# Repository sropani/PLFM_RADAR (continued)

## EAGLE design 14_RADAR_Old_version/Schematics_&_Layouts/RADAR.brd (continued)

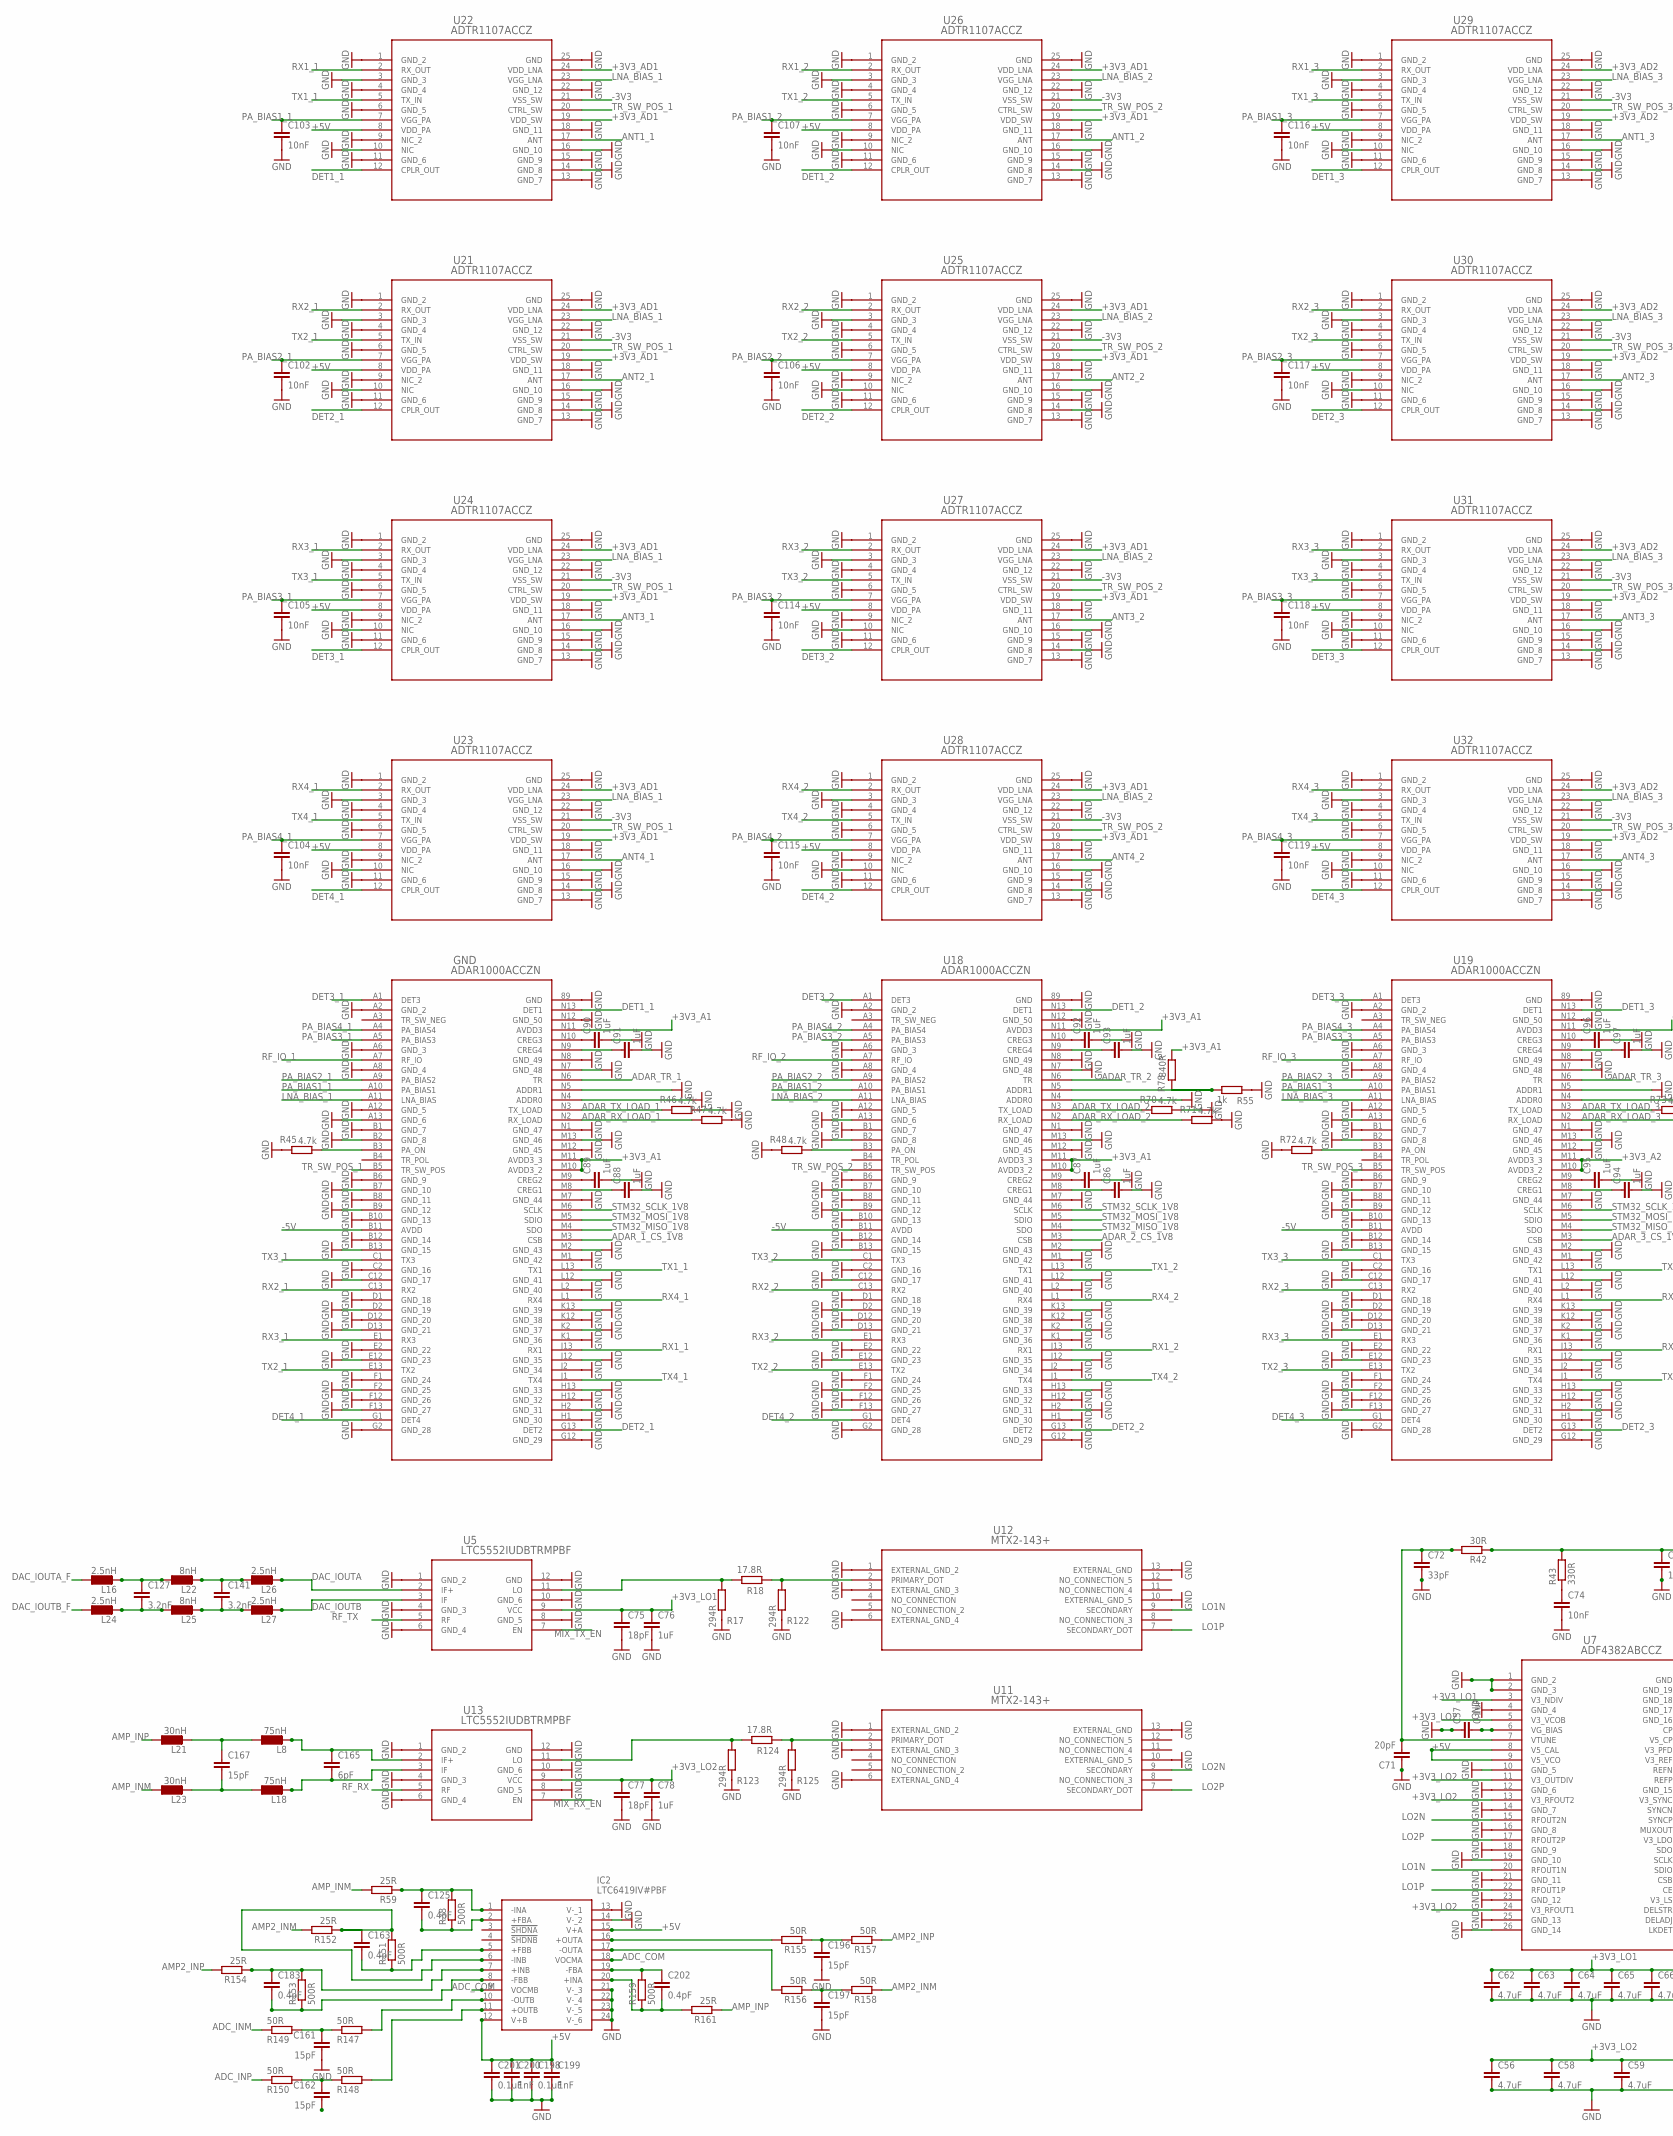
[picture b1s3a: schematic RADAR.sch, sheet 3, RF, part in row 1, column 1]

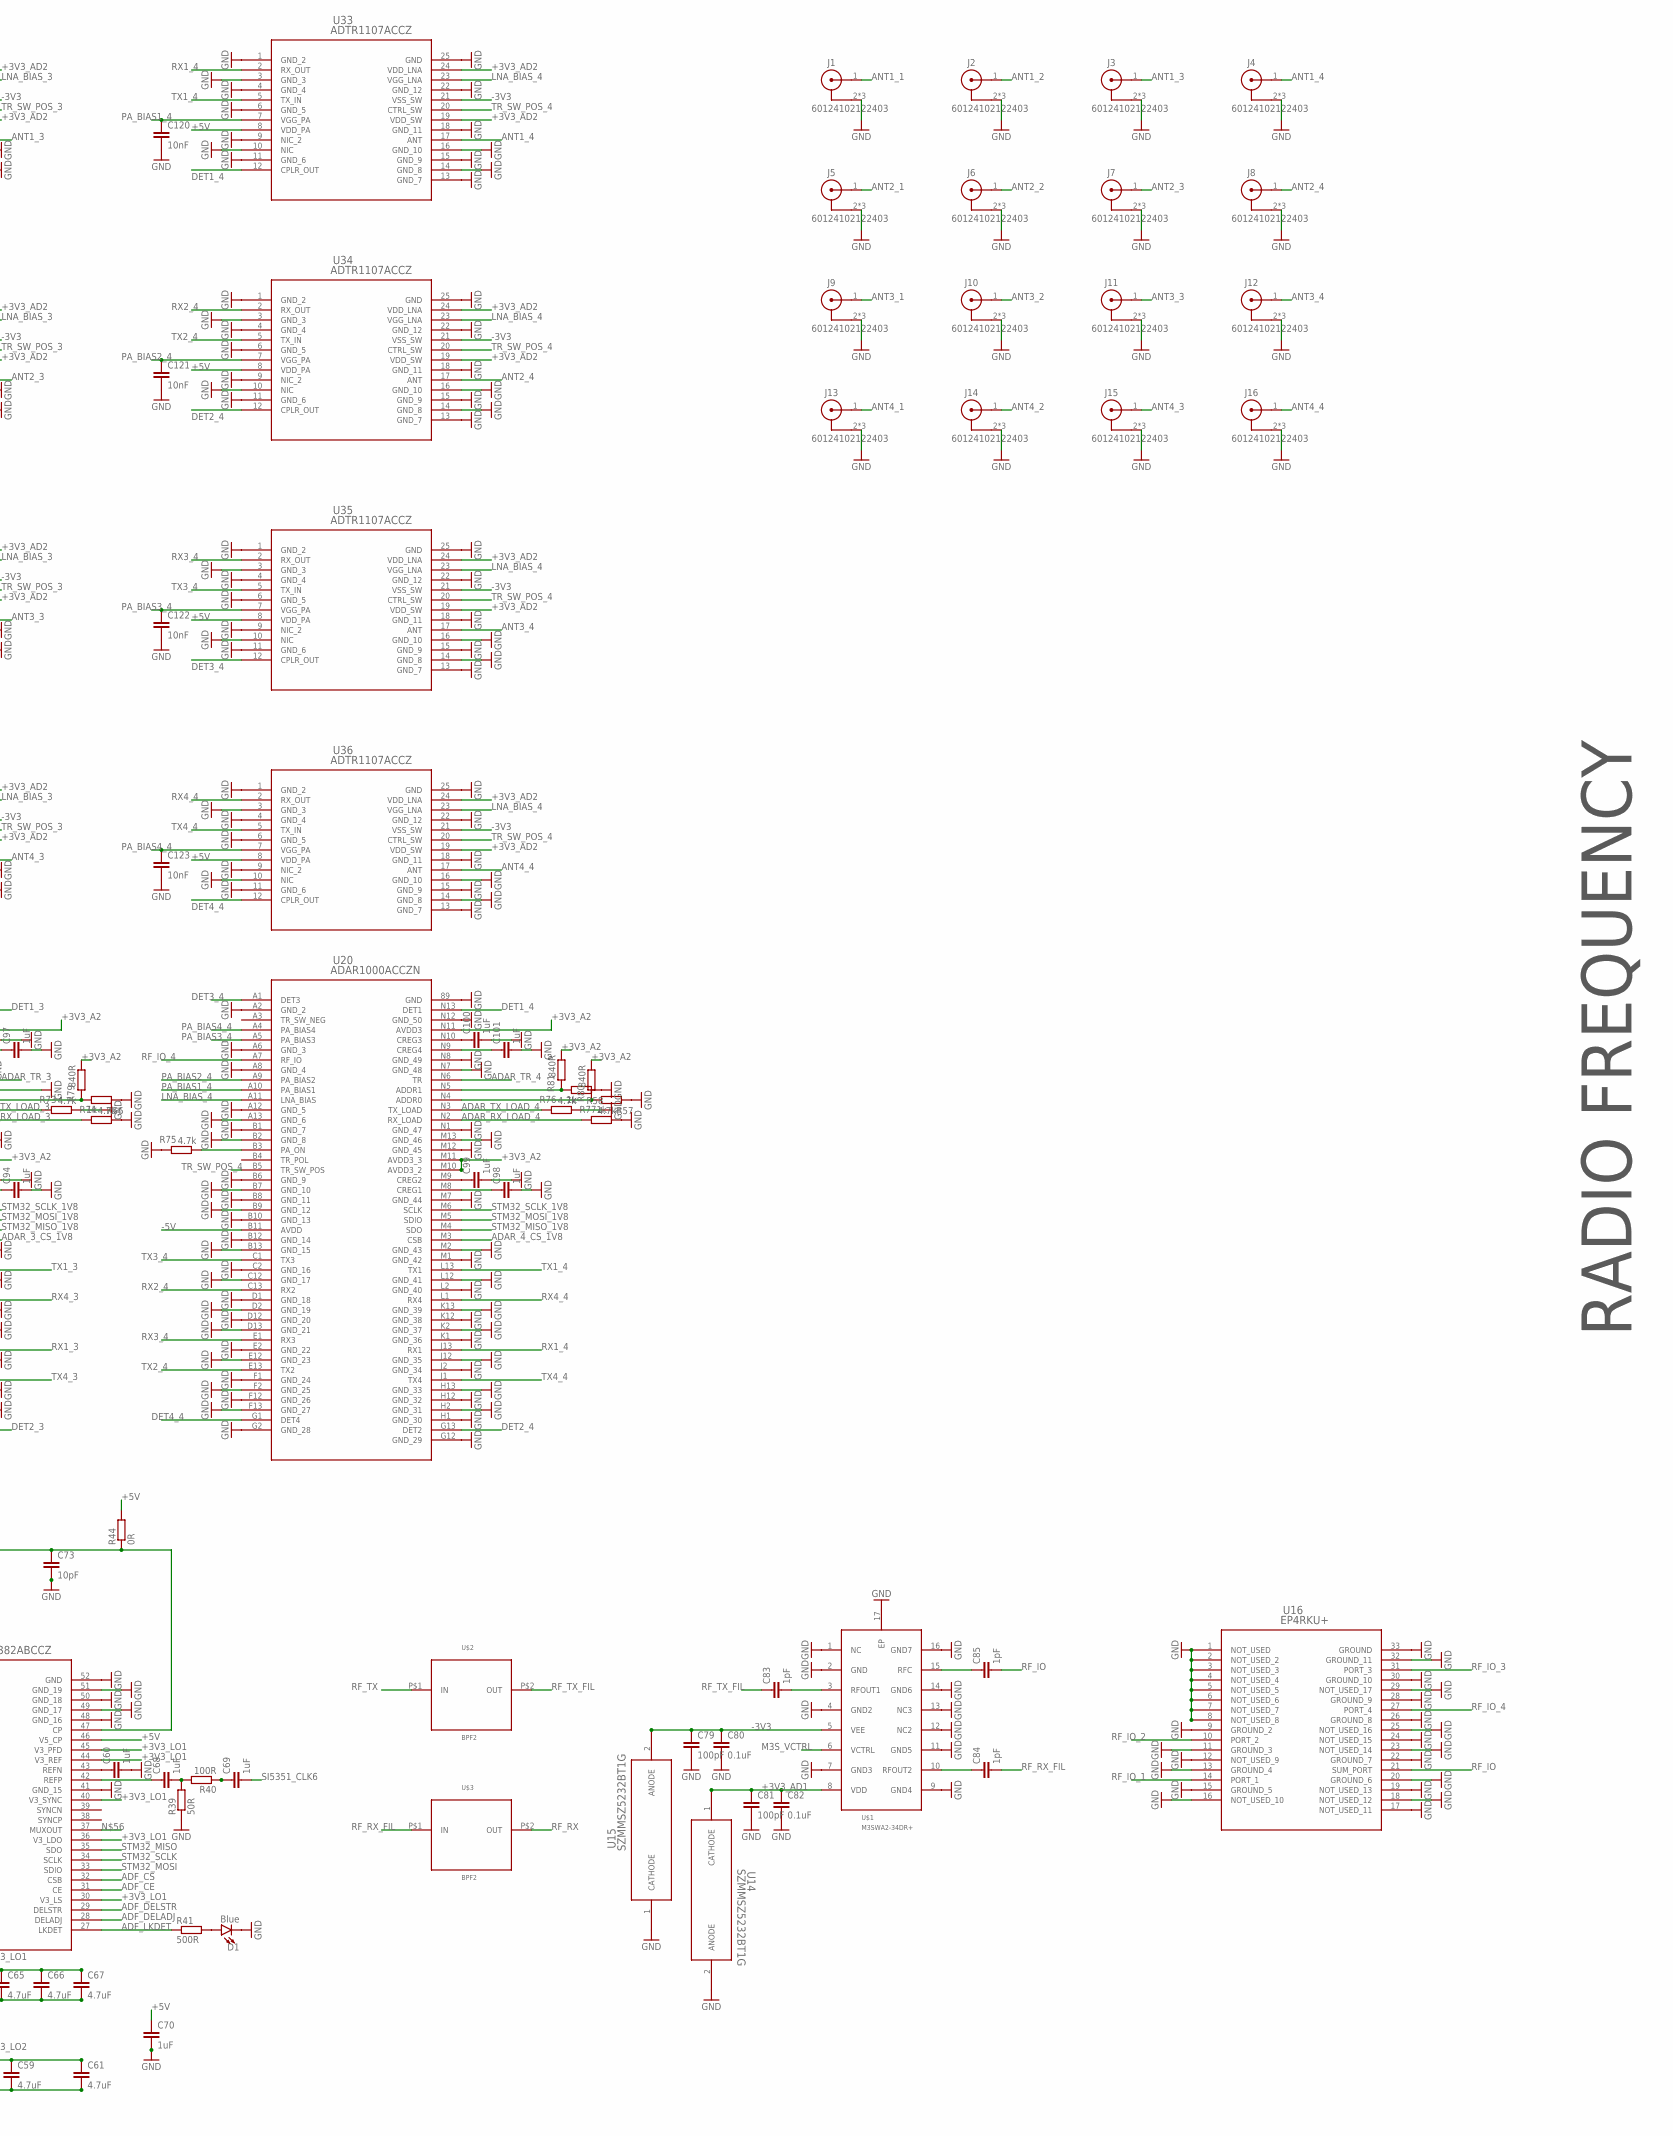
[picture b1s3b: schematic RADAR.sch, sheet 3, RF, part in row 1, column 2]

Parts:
C56, C58, C59, C61, C62, C63, C64, C65, C66, C67: 4.7uF; C0201
C57, C80, C82, C198, C201: 0.1uF; C0201
C60, C68, C69, C70, C76, C78, C86, C87, C88, C89, C90, C91, C92, C93, C94, C95, C96, C97, C98, C99, C100, C101: 1uF; C0201
C71: 20pF; C0201
C72: 33pF; C0201
C73: 10pF; C0201
C74, C102, C103, C104, C105, C106, C107, C114, C115, C116, C117, C118, C119, C120, C121, C122, C123: 10nF; C0201
C75, C77: 18pF; C0201
C79, C81: 100pF; C0201
C83, C84, C85: 1pF; C0201
C125, C163, C183, C202: 0.4pF; C0201
C127, C141: 3.2nF; C0201
C161, C162, C167, C196, C197: 15pF; C0201
C165: 6pF; C0201
C199, C200: 1nF; C0201
D1: Blue; LED-0603
GND: ADAR1000ACCZN; CC-88-1_ADI
IC2: LTC6419IV#PBF; LTC6419IVPBF
J1, J2, J3, J4, J5, J6, J7, J8, J9, J10, J11, J12, J13, J14, J15, J16: 60124102122403
L8, L18: 75nH; L0201
L16, L24, L26, L27: 2.5nH; L0201
L21, L23: 30nH; L0201
L22, L25: 8nH; L0201
R17, R122, R123, R125: 294R; R0201
R18, R124: 17.8R; R0201
R38, R41, R151, R153, R159: 500R; R0201
R39, R147, R148, R149, R150, R155, R156, R157, R158: 50R; R0201
R40: 100R; R0201
R42: 30R; R0201
R43: 330R; R0201
R44: 0R; R0201
R45, R46, R47, R48, R70, R71, R72, R73, R74, R75, R76, R77: 4.7k; R0201
R55, R56, R57, R58: 1k; R0201
R59, R152, R154, R161: 25R; R0201
R78, R79, R80, R81: 840R; R0201
U5, U13: LTC5552IUDBTRMPBF; UDB_12_ADI
U7: ADF4382ABCCZ; CC-48-10_ADI
U11, U12: MTX2-143+; DQ1225_MNC
U14, U15: SZMMSZ5232BT1G; SOD-123_ONS
U16: EP4RKU+; DG1677-2_MNC
U18, U19, U20: ADAR1000ACCZN; CC-88-1_ADI
U21, U22, U23, U24, U25, U26, U27, U28, U29, U30, U31, U32, U33, U34, U35, U36: ADTR1107ACCZ; CC-24-8_ADI
U$1: M3SWA2-34DR+; 16_QFN
U$2, U$3: BPF2

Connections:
+3V3_A1: GND.M10 (AVDD3_2), GND.M11 (AVDD3_3), GND.N11 (AVDD3), R78.1, U18.M10 (AVDD3_2), U18.M11 (AVDD3_3), U18.N11 (AVDD3); also elsewhere on the board
+3V3_A2: R79.1, R80.1, R81.1, U19.M10 (AVDD3_2), U19.M11 (AVDD3_3), U19.N11 (AVDD3), U20.M10 (AVDD3_2), U20.M11 (AVDD3_3), U20.N11 (AVDD3); also elsewhere on the board
+3V3_AD1: C81.1, C82.1, U14.1 (CATHODE), U21.19 (VDD_SW), U21.24 (VDD_LNA), U22.19 (VDD_SW), U22.24 (VDD_LNA), U23.19 (VDD_SW), U23.24 (VDD_LNA), U24.19 (VDD_SW), U24.24 (VDD_LNA), U25.19 (VDD_SW), U25.24 (VDD_LNA), U26.19 (VDD_SW), U26.24 (VDD_LNA), U27.19 (VDD_SW), U27.24 (VDD_LNA), U28.19 (VDD_SW), U28.24 (VDD_LNA), U$1.8 (VDD); also elsewhere on the board
+3V3_AD2: U29.19 (VDD_SW), U29.24 (VDD_LNA), U30.19 (VDD_SW), U30.24 (VDD_LNA), U31.19 (VDD_SW), U31.24 (VDD_LNA), U32.19 (VDD_SW), U32.24 (VDD_LNA), U33.19 (VDD_SW), U33.24 (VDD_LNA), U34.19 (VDD_SW), U34.24 (VDD_LNA), U35.19 (VDD_SW), U35.24 (VDD_LNA), U36.19 (VDD_SW), U36.24 (VDD_LNA); also elsewhere on the board
+3V3_LO1: C62.1, C63.1, C64.1, C65.1, C66.1, C67.1, C75.1, C76.1, U5.9 (VCC), U7.3 (V3_NDIV), U7.30 (V3_LS), U7.36 (V3_LDO), U7.40 (V3_SYNC), U7.44 (V3_REF), U7.45 (V3_PFD); also elsewhere on the board
+3V3_LO2: C56.1, C58.1, C59.1, C61.1, C77.1, C78.1, U7.5 (V3_VCOB), U7.11 (V3_OUTDIV), U7.13 (V3_RFOUT2), U7.24 (V3_RFOUT1), U13.9 (VCC); also elsewhere on the board
+5V: C70.1, C198.1, C199.1, C200.1, C201.1, IC2.12 (V+B), IC2.15 (V+A), R44.2, U7.8 (V5_CAL), U7.9 (V5_VCO), U7.46 (V5_CP), U21.8 (VDD_PA), U22.8 (VDD_PA), U23.8 (VDD_PA), U24.8 (VDD_PA), U25.8 (VDD_PA), U26.8 (VDD_PA), U27.8 (VDD_PA), U28.8 (VDD_PA), U29.8 (VDD_PA), U30.8 (VDD_PA), U31.8 (VDD_PA), U32.8 (VDD_PA), U33.8 (VDD_PA), U34.8 (VDD_PA), U35.8 (VDD_PA), U36.8 (VDD_PA); also elsewhere on the board
-3V3: C79.1, C80.1, U15.2 (ANODE), U21.21 (VSS_SW), U22.21 (VSS_SW), U23.21 (VSS_SW), U24.21 (VSS_SW), U25.21 (VSS_SW), U26.21 (VSS_SW), U27.21 (VSS_SW), U28.21 (VSS_SW), U29.21 (VSS_SW), U30.21 (VSS_SW), U31.21 (VSS_SW), U32.21 (VSS_SW), U33.21 (VSS_SW), U34.21 (VSS_SW), U35.21 (VSS_SW), U36.21 (VSS_SW), U$1.5 (VEE); also elsewhere on the board
-5V: GND.B11 (AVDD), U18.B11 (AVDD), U19.B11 (AVDD), U20.B11 (AVDD); also elsewhere on the board
ADAR_1_CS_1V8: GND.M3 (CSB); also elsewhere on the board
ADAR_2_CS_1V8: U18.M3 (CSB); also elsewhere on the board
ADAR_3_CS_1V8: U19.M3 (CSB); also elsewhere on the board
ADAR_4_CS_1V8: U20.M3 (CSB); also elsewhere on the board
ADAR_RX_LOAD_1: GND.N2 (RX_LOAD), R47.2; also elsewhere on the board
ADAR_RX_LOAD_2: R71.2, U18.N2 (RX_LOAD); also elsewhere on the board
ADAR_RX_LOAD_3: R74.2, U19.N2 (RX_LOAD); also elsewhere on the board
ADAR_RX_LOAD_4: R77.2, U20.N2 (RX_LOAD); also elsewhere on the board
ADAR_TR_1: GND.N6 (TR); also elsewhere on the board
ADAR_TR_2: U18.N6 (TR); also elsewhere on the board
ADAR_TR_3: U19.N6 (TR); also elsewhere on the board
ADAR_TR_4: U20.N6 (TR); also elsewhere on the board
ADAR_TX_LOAD_1: GND.N3 (TX_LOAD), R46.2; also elsewhere on the board
ADAR_TX_LOAD_2: R70.2, U18.N3 (TX_LOAD); also elsewhere on the board
ADAR_TX_LOAD_3: R73.2, U19.N3 (TX_LOAD); also elsewhere on the board
ADAR_TX_LOAD_4: R76.2, U20.N3 (TX_LOAD); also elsewhere on the board
ADC_COM: IC2.9 (VOCMB), IC2.18 (VOCMA); also elsewhere on the board
ADC_INM: R149.1; also elsewhere on the board
ADC_INP: R150.1; also elsewhere on the board
ADF_CE: U7.31 (CE); also elsewhere on the board
ADF_CS: U7.32 (CSB); also elsewhere on the board
ADF_DELADJ: U7.28 (DELADJ); also elsewhere on the board
ADF_DELSTR: U7.29 (DELSTR); also elsewhere on the board
ADF_LKDET: R41.1, U7.27 (LKDET)
AMP2_INM: R152.2, R158.1
AMP2_INP: R154.2, R157.1
AMP_INM: L23.1, R59.2
AMP_INP: L21.1, R161.1
ANT1_1: J1.1, U22.17 (ANT)
ANT1_2: J2.1, U26.17 (ANT)
ANT1_3: J3.1, U29.17 (ANT)
ANT1_4: J4.1, U33.17 (ANT)
ANT2_1: J5.1, U21.17 (ANT)
ANT2_2: J6.1, U25.17 (ANT)
ANT2_3: J7.1, U30.17 (ANT)
ANT2_4: J8.1, U34.17 (ANT)
ANT3_1: J9.1, U24.17 (ANT)
ANT3_2: J10.1, U27.17 (ANT)
ANT3_3: J11.1, U31.17 (ANT)
ANT3_4: J12.1, U35.17 (ANT)
ANT4_1: J13.1, U23.17 (ANT)
ANT4_2: J14.1, U28.17 (ANT)
ANT4_3: J15.1, U32.17 (ANT)
ANT4_4: J16.1, U36.17 (ANT)
DAC_IOUTA: L26.2, U5.2 (IF+)
DAC_IOUTA_F: L16.1; also elsewhere on the board
DAC_IOUTB: L27.2, U5.3 (IF)
DAC_IOUTB_F: L24.1; also elsewhere on the board
DET1_1: GND.N13 (DET1), U22.12 (CPLR_OUT)
DET1_2: U18.N13 (DET1), U26.12 (CPLR_OUT)
DET1_3: U19.N13 (DET1), U29.12 (CPLR_OUT)
DET1_4: U20.N13 (DET1), U33.12 (CPLR_OUT)
DET2_1: GND.G13 (DET2), U21.12 (CPLR_OUT)
DET2_2: U18.G13 (DET2), U25.12 (CPLR_OUT)
DET2_3: U19.G13 (DET2), U30.12 (CPLR_OUT)
DET2_4: U20.G13 (DET2), U34.12 (CPLR_OUT)
DET3_1: GND.A1 (DET3), U24.12 (CPLR_OUT)
DET3_2: U18.A1 (DET3), U27.12 (CPLR_OUT)
DET3_3: U19.A1 (DET3), U31.12 (CPLR_OUT)
DET3_4: U20.A1 (DET3), U35.12 (CPLR_OUT)
DET4_1: GND.G1 (DET4), U23.12 (CPLR_OUT)
DET4_2: U18.G1 (DET4), U28.12 (CPLR_OUT)
DET4_3: U19.G1 (DET4), U32.12 (CPLR_OUT)
DET4_4: U20.G1 (DET4), U36.12 (CPLR_OUT)
GND: C56.2, C57.1, C58.2, C59.2, C60.2, C61.2, C62.2, C63.2, C64.2, C65.2, C66.2, C67.2, C70.2, C71.1, C72.2, C73.2, C74.2, C75.2, C76.2, C77.2, C78.2, C79.2, C80.2, C81.2, C82.2, C86.2, C87.2, C88.2, C89.2, C90.2, C91.2, C92.2, C93.2, C94.2, C95.2, C96.2, C97.2, C98.2, C99.2, C100.2, C101.2, C102.2, C103.2, C104.2, C105.2, C106.2, C107.2, C114.2, C115.2, C116.2, C117.2, C118.2, C119.2, C120.2, C121.2, C122.2, C123.2, C161.2, C162.2, C196.2, C197.2, C198.2, C199.2, C200.2, C201.2, D1.C, GND.89 (GND), GND.A2 (GND_2), GND.A6 (GND_3), GND.A8 (GND_4), GND.A12 (GND_5), GND.A13 (GND_6), GND.B1 (GND_7), GND.B2 (GND_8), GND.B6 (GND_9), GND.B7 (GND_10), GND.B8 (GND_11), GND.B9 (GND_12), GND.B10 (GND_13), GND.B12 (GND_14), GND.B13 (GND_15), GND.C2 (GND_16), GND.C12 (GND_17), GND.D1 (GND_18), GND.D2 (GND_19), GND.D12 (GND_20), GND.D13 (GND_21), GND.E2 (GND_22), GND.E12 (GND_23), GND.F1 (GND_24), GND.F2 (GND_25), GND.F12 (GND_26), GND.F13 (GND_27), GND.G2 (GND_28), GND.G12 (GND_29), GND.H1 (GND_30), GND.H2 (GND_31), GND.H12 (GND_32), GND.H13 (GND_33), GND.J2 (GND_34), GND.J12 (GND_35), GND.K1 (GND_36), GND.K2 (GND_37), GND.K12 (GND_38), GND.K13 (GND_39), GND.L2 (GND_40), GND.L12 (GND_41), GND.M1 (GND_42), GND.M2 (GND_43), GND.M7 (GND_44), GND.M12 (GND_45), GND.M13 (GND_46), GND.N1 (GND_47), GND.N4 (ADDR0), GND.N5 (ADDR1), GND.N7 (GND_48), GND.N8 (GND_49), GND.N12 (GND_50), IC2.13 (V-_1), IC2.14 (V-_2), IC2.21 (V-_3), IC2.22 (V-_4), IC2.23 (V-_5), IC2.24 (V-_6), J1.2, J1.3 (2), J1.4 (2), J2.2, J2.3 (2), J2.4 (2), J3.2, J3.3 (2), J3.4 (2), J4.2, J4.3 (2), J4.4 (2), J5.2, J5.3 (2), J5.4 (2), J6.2, J6.3 (2), J6.4 (2), J7.2, J7.3 (2), J7.4 (2), J8.2, J8.3 (2), J8.4 (2), J9.2, J9.3 (2), J9.4 (2), J10.2, J10.3 (2), J10.4 (2), J11.2, J11.3 (2), J11.4 (2), J12.2, J12.3 (2), J12.4 (2), J13.2, J13.3 (2), J13.4 (2), J14.2, J14.3 (2), J14.4 (2), J15.2, J15.3 (2), J15.4 (2), J16.2, J16.3 (2), J16.4 (2), R17.2, R39.1, R45.2, R46.1, R47.1, R48.2, R55.2, R56.2, R57.2, R58.2, R70.1, R71.1, R72.2, R73.1, R74.1, R75.2, R76.1, R77.1, R122.2, R123.2, R125.2, U5.1 (GND_2), U5.4 (GND_3), U5.6 (GND_4), U5.8 (GND_5), U5.10 (GND_6), U5.12 (GND), U7.1 (GND_2), U7.2 (GND_3), U7.4 (GND_4), U7.10 (GND_5), U7.12 (GND_6), U7.14 (GND_7), U7.16 (GND_8), U7.18 (GND_9), U7.19 (GND_10), U7.21 (GND_11), U7.23 (GND_12), U7.25 (GND_13), U7.26 (GND_14), U7.41 (GND_15), U7.48 (GND_16), U7.49 (GND_17), U7.50 (GND_18), U7.51 (GND_19), U7.52 (GND), U11.1 (EXTERNAL_GND_2), U11.3 (EXTERNAL_GND_3), U11.6 (EXTERNAL_GND_4), U11.10 (EXTERNAL_GND_5), U11.13 (EXTERNAL_GND), U12.1 (EXTERNAL_GND_2), U12.3 (EXTERNAL_GND_3), U12.6 (EXTERNAL_GND_4), U12.10 (EXTERNAL_GND_5), U12.13 (EXTERNAL_GND), U13.1 (GND_2), U13.4 (GND_3), U13.6 (GND_4), U13.8 (GND_5), U13.10 (GND_6), U13.12 (GND), U14.2 (ANODE), U15.1 (CATHODE), U16.1 (NOT_USED), U16.2 (NOT_USED_2), U16.3 (NOT_USED_3), U16.4 (NOT_USED_4), U16.5 (NOT_USED_5), U16.6 (NOT_USED_6), U16.7 (NOT_USED_7), U16.8 (NOT_USED_8), U16.9 (GROUND_2), U16.11 (GROUND_3), U16.12 (NOT_USED_9), U16.13 (GROUND_4), U16.15 (GROUND_5), U16.16 (NOT_USED_10), U16.17 (NOT_USED_11), U16.18 (NOT_USED_12), U16.19 (NOT_USED_13), U16.20 (GROUND_6), U16.22 (GROUND_7), U16.23 (NOT_USED_14), U16.24 (NOT_USED_15), U16.25 (NOT_USED_16), U16.26 (GROUND_8), U16.28 (GROUND_9), U16.29 (NOT_USED_17), U16.30 (GROUND_10), U16.32 (GROUND_11), U16.33 (GROUND), U18.89 (GND), U18.A2 (GND_2), U18.A6 (GND_3), U18.A8 (GND_4), U18.A12 (GND_5), U18.A13 (GND_6), U18.B1 (GND_7), U18.B2 (GND_8), U18.B6 (GND_9), U18.B7 (GND_10), U18.B8 (GND_11), U18.B9 (GND_12), U18.B10 (GND_13), U18.B12 (GND_14), U18.B13 (GND_15), U18.C2 (GND_16), U18.C12 (GND_17), U18.D1 (GND_18), U18.D2 (GND_19), U18.D12 (GND_20), U18.D13 (GND_21), U18.E2 (GND_22), U18.E12 (GND_23), U18.F1 (GND_24), U18.F2 (GND_25), U18.F12 (GND_26), U18.F13 (GND_27), U18.G2 (GND_28), U18.G12 (GND_29), U18.H1 (GND_30), U18.H2 (GND_31), U18.H12 (GND_32), U18.H13 (GND_33), U18.J2 (GND_34), U18.J12 (GND_35), U18.K1 (GND_36), U18.K2 (GND_37), U18.K12 (GND_38), U18.K13 (GND_39), U18.L2 (GND_40), U18.L12 (GND_41), U18.M1 (GND_42), U18.M2 (GND_43), U18.M7 (GND_44), U18.M12 (GND_45), U18.M13 (GND_46), U18.N1 (GND_47), U18.N4 (ADDR0), U18.N7 (GND_48), U18.N8 (GND_49), U18.N12 (GND_50), U19.89 (GND), U19.A2 (GND_2), U19.A6 (GND_3), U19.A8 (GND_4), U19.A12 (GND_5), U19.A13 (GND_6), U19.B1 (GND_7), U19.B2 (GND_8), U19.B6 (GND_9), U19.B7 (GND_10), U19.B8 (GND_11), U19.B9 (GND_12), U19.B10 (GND_13), U19.B12 (GND_14), U19.B13 (GND_15), U19.C2 (GND_16), U19.C12 (GND_17), U19.D1 (GND_18), U19.D2 (GND_19), U19.D12 (GND_20), U19.D13 (GND_21), U19.E2 (GND_22), U19.E12 (GND_23), U19.F1 (GND_24), U19.F2 (GND_25), U19.F12 (GND_26), U19.F13 (GND_27), U19.G2 (GND_28), U19.G12 (GND_29), U19.H1 (GND_30), U19.H2 (GND_31), U19.H12 (GND_32), U19.H13 (GND_33), U19.J2 (GND_34), U19.J12 (GND_35), U19.K1 (GND_36), U19.K2 (GND_37), U19.K12 (GND_38), U19.K13 (GND_39), U19.L2 (GND_40), U19.L12 (GND_41), U19.M1 (GND_42), U19.M2 (GND_43), U19.M7 (GND_44), U19.M12 (GND_45), U19.M13 (GND_46), U19.N1 (GND_47), U19.N5 (ADDR1), U19.N7 (GND_48), U19.N8 (GND_49), U19.N12 (GND_50), U20.89 (GND), U20.A2 (GND_2), U20.A6 (GND_3), U20.A8 (GND_4), U20.A12 (GND_5), U20.A13 (GND_6), U20.B1 (GND_7), U20.B2 (GND_8), U20.B6 (GND_9), U20.B7 (GND_10), U20.B8 (GND_11), U20.B9 (GND_12), U20.B10 (GND_13), U20.B12 (GND_14)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; also elsewhere on the board
LNA_BIAS_1: GND.A11 (LNA_BIAS), U21.23 (VGG_LNA), U22.23 (VGG_LNA), U23.23 (VGG_LNA), U24.23 (VGG_LNA)
LNA_BIAS_2: U18.A11 (LNA_BIAS), U25.23 (VGG_LNA), U26.23 (VGG_LNA), U27.23 (VGG_LNA), U28.23 (VGG_LNA)
LNA_BIAS_3: U19.A11 (LNA_BIAS), U29.23 (VGG_LNA), U30.23 (VGG_LNA), U31.23 (VGG_LNA), U32.23 (VGG_LNA)
LNA_BIAS_4: U20.A11 (LNA_BIAS), U33.23 (VGG_LNA), U34.23 (VGG_LNA), U35.23 (VGG_LNA), U36.23 (VGG_LNA)
LO1N: U7.20 (RFOUT1N), U12.9 (SECONDARY)
LO1P: U7.22 (RFOUT1P), U12.7 (SECONDARY_DOT)
LO2N: U7.15 (RFOUT2N), U11.9 (SECONDARY)
LO2P: U7.17 (RFOUT2P), U11.7 (SECONDARY_DOT)
M3S_VCTRL: U$1.6 (VCTRL); also elsewhere on the board
MIX_RX_EN: U13.7 (EN); also elsewhere on the board
MIX_TX_EN: U5.7 (EN); also elsewhere on the board
unnamed: C125.1, IC2.1 (-INA), R38.2, R59.1
unnamed: R17.1, R18.1, U5.11 (LO)
unnamed: C83.2, U$1.3 (RFOUT1)
unnamed: C85.1, U$1.15 (RFC)
unnamed: C57.2, U7.6 (VG_BIAS)
unnamed: C84.1, U$1.10 (RFOUT2)
unnamed: GND.B3 (PA_ON), R45.1
unnamed: R48.1, U18.B3 (PA_ON)
unnamed: C165.1, L8.2, U13.2 (IF+)
unnamed: C87.1, U18.M9 (CREG2)
unnamed: C73.1, R42.1, R43.2, R44.1, U7.47 (CP)
unnamed: C71.2, C72.1, R42.2, U7.7 (VTUNE)
unnamed: C86.1, U18.M8 (CREG1)
unnamed: C92.1, U18.N10 (CREG3)
unnamed: C165.2, L18.2, U13.3 (IF)
unnamed: C60.1, U7.43 (REFN)
unnamed: C68.2, R39.2, R40.2
unnamed: C69.1, R40.1
unnamed: C68.1, U7.42 (REFP)
unnamed: C93.1, U18.N9 (CREG4)
unnamed: R72.1, U19.B3 (PA_ON)
unnamed: C167.1, L8.1, L21.2
unnamed: C95.1, U19.M9 (CREG2)
unnamed: C94.1, U19.M8 (CREG1)
unnamed: C96.1, U19.N10 (CREG3)
unnamed: C167.2, L18.1, L23.2
unnamed: C97.1, U19.N9 (CREG4)
unnamed: R75.1, U20.B3 (PA_ON)
unnamed: R18.2, R122.1, U12.2 (PRIMARY_DOT)
unnamed: C91.1, GND.N9 (CREG4)
unnamed: D1.A, R41.2
unnamed: C99.1, U20.M9 (CREG2)
unnamed: C98.1, U20.M8 (CREG1)
unnamed: C100.1, U20.N10 (CREG3)
unnamed: C74.1, R43.1
unnamed: R123.1, R124.1, U13.11 (LO)
unnamed: R124.2, R125.1, U11.2 (PRIMARY_DOT)
unnamed: C127.1, L16.2, L22.1
unnamed: C101.1, U20.N9 (CREG4)
unnamed: C89.1, GND.M9 (CREG2)
unnamed: C88.1, GND.M8 (CREG1)
unnamed: C125.2, IC2.2 (+FBA), R38.1
unnamed: C90.1, GND.N10 (CREG3)
unnamed: R55.1, R78.2, U18.N5 (ADDR1)
unnamed: R56.1, R79.2, U19.N4 (ADDR0)
unnamed: R58.1, R81.2, U20.N5 (ADDR1)
unnamed: R57.1, R80.2, U20.N4 (ADDR0)
unnamed: C141.1, L22.2, L26.1
unnamed: C127.2, L24.2, L25.1
unnamed: C141.2, L25.2, L27.1
unnamed: C161.1, R147.1, R149.2
unnamed: C162.1, R148.1, R150.2
unnamed: IC2.10 (-OUTB), R147.2
unnamed: IC2.11 (+OUTB), R148.2
unnamed: C163.1, IC2.6 (-INB), R151.2, R152.1
unnamed: C163.2, IC2.5 (+FBB), R151.1
unnamed: C183.1, IC2.7 (+INB), R153.2, R154.1
unnamed: C183.2, IC2.8 (-FBB), R153.1
unnamed: IC2.16 (+OUTA), R155.2
unnamed: IC2.17 (-OUTA), R156.2
unnamed: C196.1, R155.1, R157.2
unnamed: C197.1, R156.1, R158.2
unnamed: C202.2, IC2.20 (+INA), R159.1, R161.2
unnamed: C202.1, IC2.19 (-FBA), R159.2
PA_BIAS1_1: C103.1, GND.A10 (PA_BIAS1), U22.7 (VGG_PA)
PA_BIAS1_2: C107.1, U18.A10 (PA_BIAS1), U26.7 (VGG_PA)
PA_BIAS1_3: C116.1, U19.A10 (PA_BIAS1), U29.7 (VGG_PA)
PA_BIAS1_4: C120.1, U20.A10 (PA_BIAS1), U33.7 (VGG_PA)
PA_BIAS2_1: C102.1, GND.A9 (PA_BIAS2), U21.7 (VGG_PA)
PA_BIAS2_2: C106.1, U18.A9 (PA_BIAS2), U25.7 (VGG_PA)
PA_BIAS2_3: C117.1, U19.A9 (PA_BIAS2), U30.7 (VGG_PA)
PA_BIAS2_4: C121.1, U20.A9 (PA_BIAS2), U34.7 (VGG_PA)
PA_BIAS3_1: C105.1, GND.A5 (PA_BIAS3), U24.7 (VGG_PA)
PA_BIAS3_2: C114.1, U18.A5 (PA_BIAS3), U27.7 (VGG_PA)
PA_BIAS3_3: C118.1, U19.A5 (PA_BIAS3), U31.7 (VGG_PA)
PA_BIAS3_4: C122.1, U20.A5 (PA_BIAS3), U35.7 (VGG_PA)
PA_BIAS4_1: C104.1, GND.A4 (PA_BIAS4), U23.7 (VGG_PA)
PA_BIAS4_2: C115.1, U18.A4 (PA_BIAS4), U28.7 (VGG_PA)
PA_BIAS4_3: C119.1, U19.A4 (PA_BIAS4), U32.7 (VGG_PA)
PA_BIAS4_4: C123.1, U20.A4 (PA_BIAS4), U36.7 (VGG_PA)
RF_IO: C85.2, U16.21 (SUM_PORT)
RF_IO_1: GND.A7 (RF_IO), U16.14 (PORT_1)
RF_IO_2: U16.10 (PORT_2), U18.A7 (RF_IO)
RF_IO_3: U16.31 (PORT_3), U19.A7 (RF_IO)
RF_IO_4: U16.27 (PORT_4), U20.A7 (RF_IO)
RF_RX: U13.5 (RF), U$3.P$2 (OUT)
RF_RX_FIL: C84.2, U$3.P$1 (IN)
RF_TX: U5.5 (RF), U$2.P$1 (IN)
RF_TX_FIL: C83.1, U$2.P$2 (OUT)
RX1_1: GND.J13 (RX1), U22.2 (RX_OUT)
RX1_2: U18.J13 (RX1), U26.2 (RX_OUT)
RX1_3: U19.J13 (RX1), U29.2 (RX_OUT)
RX1_4: U20.J13 (RX1), U33.2 (RX_OUT)
RX2_1: GND.C13 (RX2), U21.2 (RX_OUT)
RX2_2: U18.C13 (RX2), U25.2 (RX_OUT)
RX2_3: U19.C13 (RX2), U30.2 (RX_OUT)
RX2_4: U20.C13 (RX2), U34.2 (RX_OUT)
RX3_1: GND.E1 (RX3), U24.2 (RX_OUT)
RX3_2: U18.E1 (RX3), U27.2 (RX_OUT)
RX3_3: U19.E1 (RX3), U31.2 (RX_OUT)
RX3_4: U20.E1 (RX3), U35.2 (RX_OUT)
RX4_1: GND.L1 (RX4), U23.2 (RX_OUT)
RX4_2: U18.L1 (RX4), U28.2 (RX_OUT)
RX4_3: U19.L1 (RX4), U32.2 (RX_OUT)
RX4_4: U20.L1 (RX4), U36.2 (RX_OUT)
SI5351_CLK6: C69.2; also elsewhere on the board
STM32_MISO: U7.35 (SDO); also elsewhere on the board
STM32_MISO_1V8: GND.M4 (SDO), U18.M4 (SDO), U19.M4 (SDO), U20.M4 (SDO); also elsewhere on the board
STM32_MOSI: U7.33 (SDIO); also elsewhere on the board
STM32_MOSI_1V8: GND.M5 (SDIO), U18.M5 (SDIO), U19.M5 (SDIO), U20.M5 (SDIO); also elsewhere on the board
STM32_SCLK: U7.34 (SCLK); also elsewhere on the board
STM32_SCLK_1V8: GND.M6 (SCLK), U18.M6 (SCLK), U19.M6 (SCLK), U20.M6 (SCLK); also elsewhere on the board
TR_SW_POS_1: GND.B5 (TR_SW_POS), U21.20 (CTRL_SW), U22.20 (CTRL_SW), U23.20 (CTRL_SW), U24.20 (CTRL_SW)
TR_SW_POS_2: U18.B5 (TR_SW_POS), U25.20 (CTRL_SW), U26.20 (CTRL_SW), U27.20 (CTRL_SW), U28.20 (CTRL_SW)
TR_SW_POS_3: U19.B5 (TR_SW_POS), U29.20 (CTRL_SW), U30.20 (CTRL_SW), U31.20 (CTRL_SW), U32.20 (CTRL_SW)
TR_SW_POS_4: U20.B5 (TR_SW_POS), U33.20 (CTRL_SW), U34.20 (CTRL_SW), U35.20 (CTRL_SW), U36.20 (CTRL_SW)
TX1_1: GND.L13 (TX1), U22.5 (TX_IN)
TX1_2: U18.L13 (TX1), U26.5 (TX_IN)
TX1_3: U19.L13 (TX1), U29.5 (TX_IN)
TX1_4: U20.L13 (TX1), U33.5 (TX_IN)
TX2_1: GND.E13 (TX2), U21.5 (TX_IN)
TX2_2: U18.E13 (TX2), U25.5 (TX_IN)
TX2_3: U19.E13 (TX2), U30.5 (TX_IN)
TX2_4: U20.E13 (TX2), U34.5 (TX_IN)
TX3_1: GND.C1 (TX3), U24.5 (TX_IN)
TX3_2: U18.C1 (TX3), U27.5 (TX_IN)
TX3_3: U19.C1 (TX3), U31.5 (TX_IN)
TX3_4: U20.C1 (TX3), U35.5 (TX_IN)
TX4_1: GND.J1 (TX4), U23.5 (TX_IN)
TX4_2: U18.J1 (TX4), U28.5 (TX_IN)
TX4_3: U19.J1 (TX4), U32.5 (TX_IN)
TX4_4: U20.J1 (TX4), U36.5 (TX_IN)

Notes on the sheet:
RADIO FREQUENCY

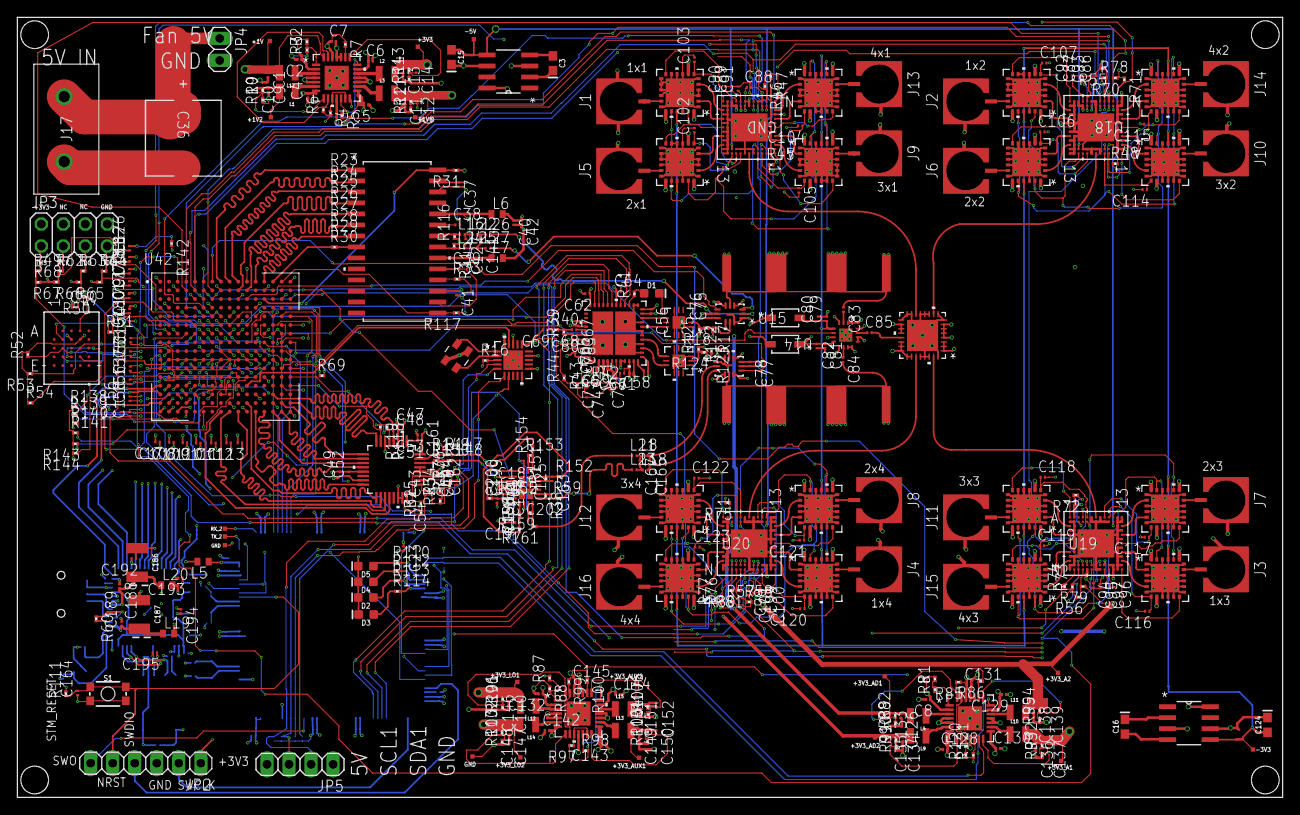
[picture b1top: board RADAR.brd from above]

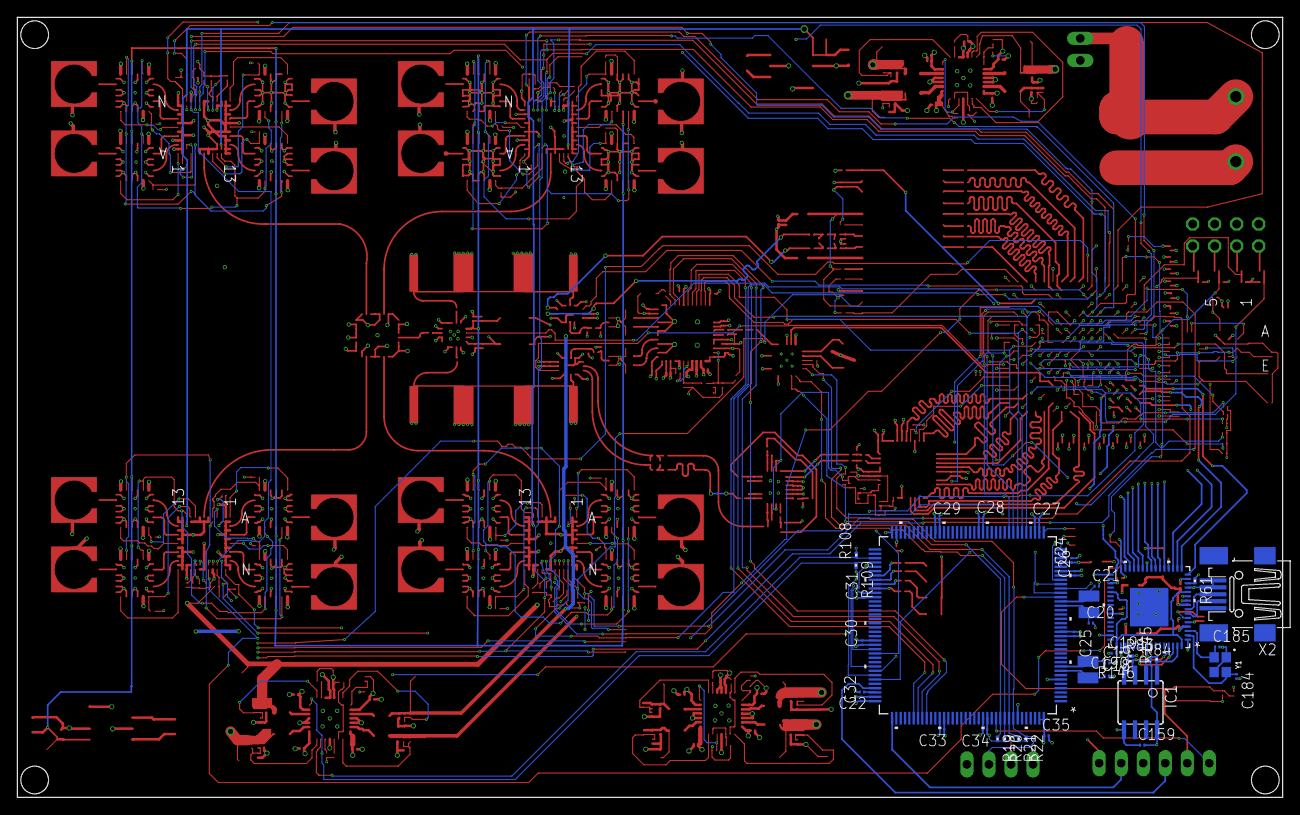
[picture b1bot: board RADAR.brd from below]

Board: 6 copper layers, 146.0 x 90.0 mm, 462 parts (40 on the bottom side), 398 nets.

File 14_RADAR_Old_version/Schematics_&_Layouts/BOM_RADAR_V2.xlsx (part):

Qty | Value | Device | Package | Parts | Description | MANUFACTURER_PART_NUMBER
1 |  | PINHD-1X6 | 1X06 | JP2 | PIN HEADER | M20-9990645
1 |  | PINHD-2X4 | 2X04 | JP3 | PIN HEADER | 67997-208HLF
24 | 0.1uF | CC0201 | C0201 | C38, C39, C41, C42, C43, C44, C45, C47, C49, C53, C54, C57, C80, C82, C141, C15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 | CAPACITOR, European symbol | CL03A104KP3NNNH
12 | 0.47uF | CC0201 | C0201 | C110, C111, C112, C113, C155, C156, C157, C158, C179, C180, C181, C182 | CAPACITOR, European symbol | CL03A474KP3NNNC
4 | 0.4pF | CC0201 | C0201 | C3, C127, C174, C175 | CAPACITOR, European symbol | CC0201BRNPO9BNR40
1 | 0R | RR0201 | R0201 | R44 | RESISTOR, European symbol | RC0201JR-070RL
12 | 1.5ｵH | 2.2ｵH_SHIELDED_INDUCTOR | 806 | L1, L2, L3, L4, L9, L10, L11, L12, L13, L14, L15, L17 | Murata 2.2uH Inductor | LQM2MPN1R5MGHL
1 | 1.9k | RR0201 | R0201 | R35 | RESISTOR, European symbol | ERJ-1GNF1911C
1 | 100R | RR0201 | R0201 | R40 | RESISTOR, European symbol | RC0201FR-07100RL
12 | 100nF | CC0201 | C0201 | C24, C25, C26, C27, C28, C29, C30, C32, C33, C34, C35, C50 | CAPACITOR, European symbol | CL03A104KP3NNNH
2 | 100pF | CC0201 | C0201 | C79, C81 | CAPACITOR, European symbol | 0201CG101J500NT
1 | 100ｵF | UCD1H101MNL1GS | PCAP_8X10-ELECT_NCA | C36 |  | UCD1H101MNL1GS
33 | 10k | RR0201 | R0201 | R4, R5, R6, R7, R10, R12, R14, R19, R20, R21, R22, R83, R84, R85, R86, R89, R91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 | RESISTOR, European symbol | AC0201FR-0710KL
17 | 10nF | CC0201 | C0201 | C74, C102, C103, C104, C105, C106, C107, C114, C115, C116, C117, C118, C119, C1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 | CAPACITOR, European symbol | 0201B103K250NT
1 | 10pF | CC0201 | C0201 | C73 | CAPACITOR, European symbol | CL03C100JA3GNNC
2 | 10uF | CC0201 | C0201 | C37, C40 | CAPACITOR, European symbol | KGM03DS60E106MH
2 | 12pF | CC0201 | C0201 | C184, C185 | CAPACITOR, European symbol | Please suggest part
14 | 15pF | CC0201 | C0201 | C14, C133, C135, C137, C139, C146, C148, C150, C152, C167, C168, C169, C170, C1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 | CAPACITOR, European symbol | Please suggest part
3 | 18pF | CC0201 | C0201 | C12, C75, C77 | CAPACITOR, European symbol | Please suggest part
16 | 1k | RR0201 | R0201 | R15, R16, R17, R18, R34, R36, R37, R55, R56, R57, R58, R61, R138, R139, R140, R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 | RESISTOR, European symbol | Please suggest part
1 | 1k2_1% | RR0201 | R0201 | R60 | RESISTOR, European symbol | Please suggest part
2 | 1nF | CC0201 | C0201 | C166, C172 | CAPACITOR, European symbol | Please suggest part
3 | 1pF | CC0201 | C0201 | C83, C84, C85 | CAPACITOR, European symbol | Please suggest part
25 | 1uF | CC0201 | C0201 | C7, C60, C68, C69, C70, C76, C78, C86, C87, C88, C89, C90, C91, C92, C93, C94, 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 | CAPACITOR, European symbol | Please suggest part
1 | 2.2k | RR0201 | R0201 | R146 | RESISTOR, European symbol | Please suggest part
7 | 2.2uF | CC0201 | C0201 | C22, C23, C46, C48, C51, C52, C164 | CAPACITOR, European symbol | Please suggest part
2 | 2.7pF | CC0201 | C0201 | C18, C19 | CAPACITOR, European symbol | Please suggest part
3 | 20k | RR0201 | R0201 | R2, R8, R88 | RESISTOR, European symbol | Please suggest part
1 | 20pF | CC0201 | C0201 | C71 | CAPACITOR, European symbol | CC0201JRNPO9BN200
13 | 22R | RR0201 | R0201 | R23, R24, R25, R26, R27, R28, R29, R30, R49, R51, R62, R63, R64 | RESISTOR, European symbol | RC0201FR-0722RL
9 | 23k | RR0201 | R0201 | R13, R82, R90, R92, R94, R96, R102, R104, R106 | RESISTOR, European symbol | WR02X2302FAL
4 | 25R | RR0201 | R0201 | R123, R125, R135, R137 | RESISTOR, European symbol | RK73H1HRTTCM25R5F
1 | 2k | RR0201 | R0201 | R9 | RESISTOR, European symbol | RC0201FR-072KL
1 | 3.3uF | CC0201 | C0201 | C191 | CAPACITOR, European symbol | Please suggest part
1 | 30R | RR0201 | R0201 | R42 | RESISTOR, European symbol | RC0201FR-0730RL
2 | 30nH | LL0201 | L0201 | L21, L23 | INDUCTOR, European symbol | LQP03TN30NH02D
1 | 330R | RR0201 | R0201 | R43 | RESISTOR, European symbol | RC0201FR-07330RL
1 | 33pF | CC0201 | C0201 | C72 | CAPACITOR, European symbol | TCC0201COG330K500ZT
1 | 3k2 | RR0201 | R0201 | R33 | RESISTOR, European symbol | ERJ-1GNF3241C
2 | 4.3pF | CC0201 | C0201 | C20, C21 | CAPACITOR, European symbol | 0201CG4R3C500NT
27 | 4.7k | RR0201 | R0201 | R45, R46, R47, R48, R50, R52, R53, R54, R65, R66, R67, R68, R69, R70, R71, R72,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 | RESISTOR, European symbol | RC0201FR-074K7L
28 | 4.7uF | CC0201 | C0201 | C2, C4, C5, C6, C8, C56, C58, C59, C61, C62, C63, C64, C65, C66, C67, C108, C10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 | CAPACITOR, European symbol | GRM035R60J475ME15D
2 | 4.7uF 35V | 4.7UF-POLAR-EIA3528-35V-10%(TANT) | EIA3528 | C186, C187 |  | TCC0201X5R473K160ZT
1 | 47nF | CC0201 | C0201 | C31 | CAPACITOR, European symbol | Please suggest part
19 | 47uF | CC0201 | C0201 | C1, C9, C11, C13, C15, C16, C17, C55, C124, C125, C126, C134, C136, C138, C140,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 | CAPACITOR, European symbol | T495C226K010AHE245
9 | 500R | RR0201 | R0201 | R41, R110, R112, R113, R114, R122, R124, R134, R136 | RESISTOR, European symbol | ERJ-1GNF4990C
12 | 50R | RR0201 | R0201 | R31, R39, R115, R116, R126, R127, R128, R129, R130, R131, R132, R133 | RESISTOR, European symbol | TNPR020150R0DEED
1 | 525R | RR0201 | R0201 | R32 | RESISTOR, European symbol | CRCW0201523RFNED
3 | 5k | RR0201 | R0201 | R1, R3, R87 | RESISTOR, European symbol | WR02X4991FAL
16 | 60124102122403 | 60124102122403 | 60124102122403 | J1, J2, J3, J4, J5, J6, J7, J8, J9, J10, J11, J12, J13, J14, J15, J16 | WR-SMP Straight | 60124102122403
1 | 691137910002 | 691137910002 | 691137910002 | J17 | Wurth Elektronik 1379, 2 Way PCB Terminal Block | 691137910002
1 | 6pF | CC0201 | C0201 | C165 | CAPACITOR, European symbol | 0201CG6R0C250NT
2 | 75nH | LL0201 | L0201 | L8, L18 | INDUCTOR, European symbol | LQP03TN75NJ02D
1 | 75pF | CC0201 | C0201 | C10 | CAPACITOR, European symbol | GRM0335C1H750GA01D
4 | 840R | RR0201 | R0201 | R78, R79, R80, R81 | RESISTOR, European symbol | CPF0201B845RE1
1 | 8k | RR0201 | R0201 | R11 | RESISTOR, European symbol | RT0201BRE078K06L
1 | AD9708AR | AD9708AR | RW_28_ADI | U3 |  | AD9708AR
4 | ADAR1000ACCZN | ADAR1000ACCZN | CC-88-1_ADI | GND, U18, U19, U20 |  | ADAR1000ACCZN
1 | ADF4382ABCCZ | ADF4382ABCCZ | CC-48-10_ADI | U7 |  | ADF4382ABCCZ
16 | ADTR1107ACCZ | ADTR1107ACCZ | CC-24-8_ADI | U21, U22, U23, U24, U25, U26, U27, U28, U29, U30, U31, U32, U33, U34, U35, U36 |  | ADTR1107ACCZ
1 | AT93C46A-10SQ-2.7 | AT93C46A-10SQ-2.7 | SOIC8 | IC1 | Three-wire Automotive Temperature Serial EEPROM 1K (64 x 16) | AT93C46A-10SQ-2.7
5 | BLM15HB121SN1 | BLM15HB121SN1 | 402 | L5, L6, L7, L19, L20 | EMIFIL (R) Chip Ferrite Bead for GHz Noise | BLM15HB121SN1
2 | BPFILTER | BPFILTER | STUB | U$2, U$3 |  | DNP
5 | Blue | LED-BLUE0603 | LED-0603 | D1, D2, D3, D4, D5 | Blue SMD LED | please suggest 0603 bue led
1 | CX3225SB25000D0FLJCC | CX3225SB25000D0FLJZ1 | XTAL4_CX3225SB_AVX | XTAL4 |  | CX3225SB25000D0FLJZ1
1 | ECS-120-10-36B2-JTN-TR | CRYSTAL-12MHZ | CRYSTAL-SMD-2X2.5MM | Y1 | 12.0MHz Crystal | ECS-120-10-36B2-JTN-TR
1 | EP4RKU+ | EP4RKU+ | DG1677-2_MNC | U16 |  | EP4RKU+
1 | FAN | PINHD-1X2 | 1X02 | JP4 | PIN HEADER | 77311-118-02LF
1 | FT2232HQ | FT2232HQ | 64QFN_FT2232HQ_FTD | U6 |  | FT2232HQ
1 | LCD | PINHD-1X4 | 1X04 | JP5 | PIN HEADER | 77311-102-04LF
2 | LM2662MX/NOPB | LM2662MX/NOPB | M08A | U8, U37 |  | LM2662MX/NOPB
2 | LTC5552IUDBTRMPBF | LTC5552IUDBTRMPBF | UDB_12_ADI | U5, U13 |  | LTC5552IUDB#TRMPBF
1 | LTC6419IVPBF | LTC6419IVPBF | LQFN_20_ADI | U41 |  | LTC6419IV#PBF
1 | M3SWA2-34DR+ | M3SWA2-34DR+ | 16_QFN | U$1 |  | M3SWA2-34DR+
1 | MAX1449EHJ+ | MAX1449EHJ+ | 21-0110B_MXM | U4 |  | MAX1449EHJ+
3 | MAX20029ATIA/V+ | MAX20029ATIA/V+ | 21-0140L_T2855-5_MXM | U1, U38, U39 |  | MAX20029ATIA/V+
1 | MINI-USB-32005-201 | MINI-USB-32005-201 | 32005-201 | X2 | MINI USB-B Conector | 10118192-0002LF
1 | MOMENTARY-SWITCH-SPST-SMD-4.6X2.8MM | MOMENTARY-SWITCH-SPST-SMD-4.6X2.8MM | TACTILE_SWITCH_SMD_4.6X2.8MM | S1 | Momentary Switch (Pushbutton) - SPST | KMR211GLFS
1 | MT25QL01GBBB8E12-0AUT | MT25QL01GBBB8E12-0AUT | BGA24_MT25QL_MRN | U9 |  | MT25QL01GBBB8E12-0AUT
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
